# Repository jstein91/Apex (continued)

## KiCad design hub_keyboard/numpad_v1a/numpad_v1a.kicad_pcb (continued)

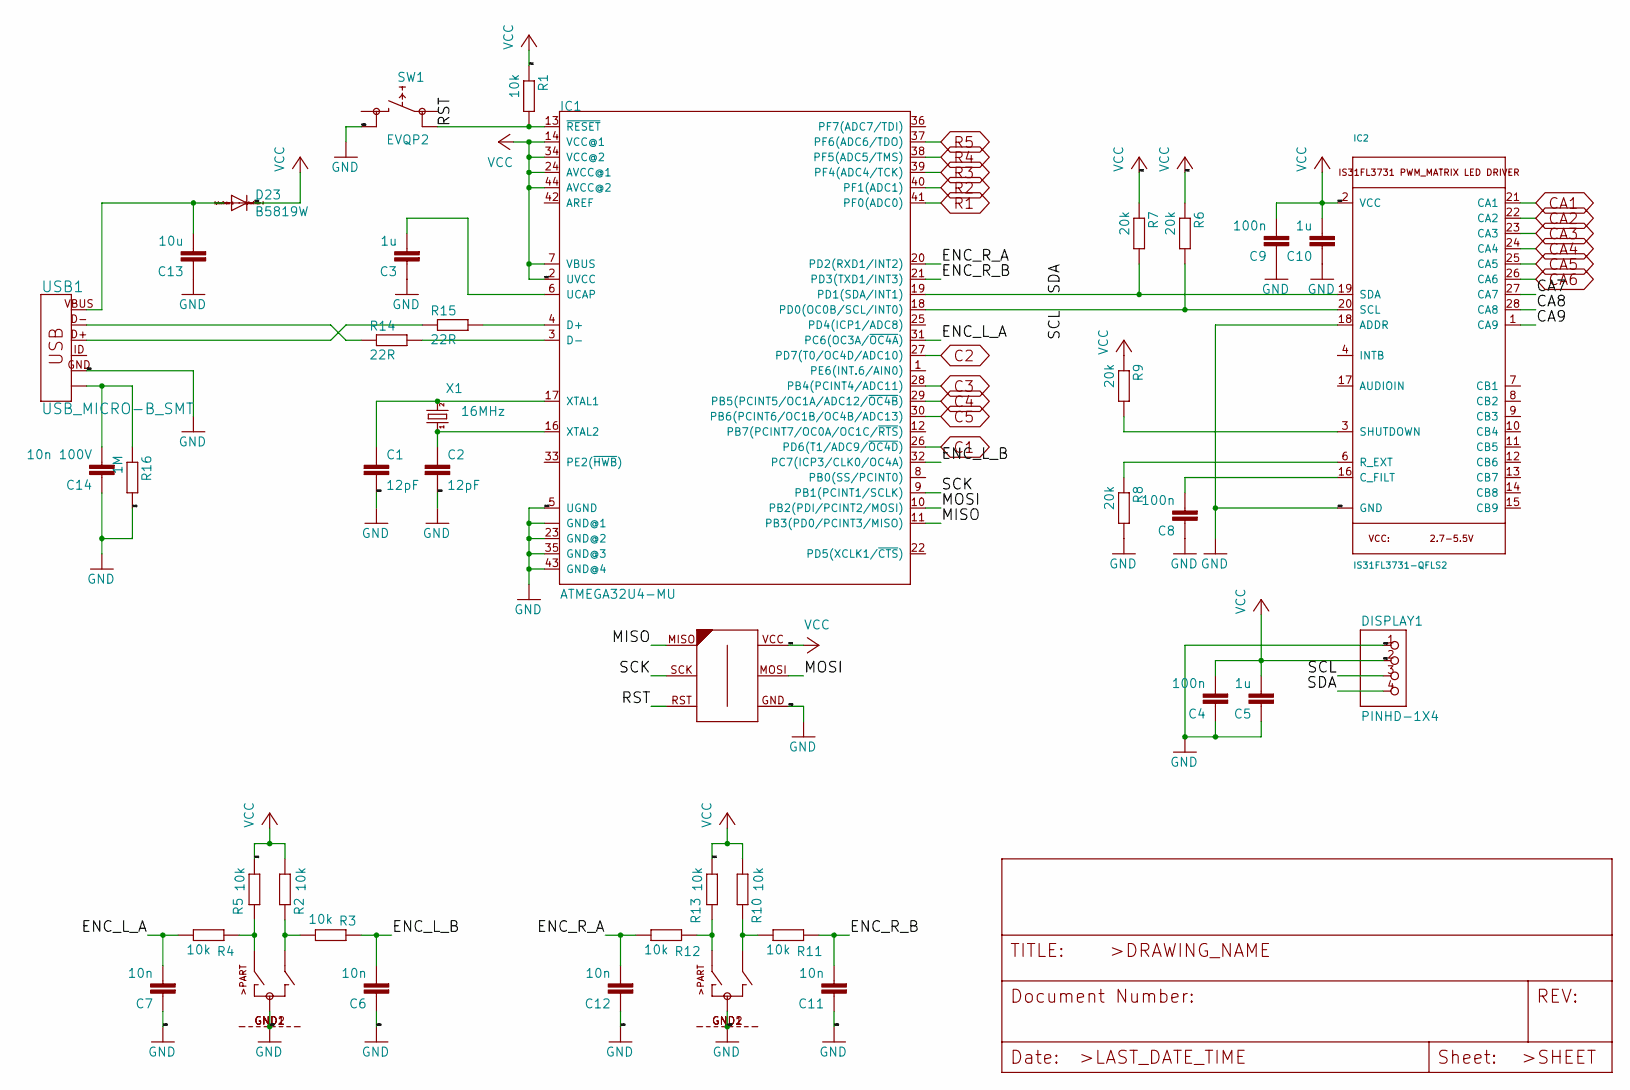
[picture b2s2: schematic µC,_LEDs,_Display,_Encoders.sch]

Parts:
C1, C2: 12pF; C0603; LCSC C38523
C3, C5, C10: 1u; C0603; LCSC C15849
C4, C8, C9: 100n; C0603; LCSC C14663
C6, C7, C11, C12: 10n; C0603; LCSC C57112
C13: 10u; C0603; LCSC C19702
C14: 10n 100V; C0603; LCSC C84709
D23: B5819W; SOD123; LCSC C8598
DISPLAY: PINHD-1X4; 1X04
ENC1, ENC2: EC12E_SW; ALPS_EC12E_SW
IC1: ATMEGA32U4-MU; QFN44G-0.5-7X7MM; LCSC C112161
IC2: IS31FL3731-QFLS2; QFN28_4MM_0.4MM
ISP: AVR-ISP-6-EDGE; 6PAD_ISP
R1, R2, R3, R4, R5, R10, R11, R12, R13: 10k; R0603; LCSC C25804
R6, R7, R8, R9: 20k; R0603; LCSC C4184
R14, R15: 22R; R0603; LCSC C23345
R16: 1M; R0603; LCSC C22935
SW1: EVQP2; FARNELL 2079559
USB: USB_MICRO-B_SMT; USB-MICROB; DIGIKEY 609-4052-1-ND
X1: 16MHz; 3.2X2.5_KX-7; LCSC C13738

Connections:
/µC, LEDs, Display, Encoders/CA7: IC2.27 (CA7)
/µC, LEDs, Display, Encoders/CA8: IC2.28 (CA8)
/µC, LEDs, Display, Encoders/CA9: IC2.1 (CA9)
/µC, LEDs, Display, Encoders/ENC_L_A: C7.2, IC1.31 (PC6(OC3A/~OC4A)), R4.1
/µC, LEDs, Display, Encoders/ENC_L_B: C6.2, IC1.32 (PC7(ICP3/CLK0/OC4A)), R3.2
/µC, LEDs, Display, Encoders/ENC_R_A: C12.2, IC1.20 (PD2(RXD1/INT2)), R12.1
/µC, LEDs, Display, Encoders/ENC_R_B: C11.2, IC1.21 (PD3(TXD1/INT3)), R11.2
/µC, LEDs, Display, Encoders/MISO: IC1.11 (PB3(PD0/PCINT3/MISO)); also elsewhere on the board
/µC, LEDs, Display, Encoders/MOSI: IC1.10 (PB2(PDI/PCINT2/MOSI)); also elsewhere on the board
/µC, LEDs, Display, Encoders/RST: IC1.13 (~RESET), R1.2, SW1.3 (0@B); also elsewhere on the board
/µC, LEDs, Display, Encoders/SCK: IC1.9 (PB1(PCINT1/SCLK)); also elsewhere on the board
/µC, LEDs, Display, Encoders/SCL: IC1.18 (PD0(OC0B/SCL/INT0)), IC2.20 (SCL), R6.2; also elsewhere on the board
/µC, LEDs, Display, Encoders/SDA: IC1.19 (PD1(SDA/INT1)), IC2.19 (SDA), R7.2; also elsewhere on the board
C1: IC1.26 (PD6(T1/ADC9/~OC4D)); also elsewhere on the board
C2: IC1.27 (PD7(T0/OC4D/ADC10)); also elsewhere on the board
C3: IC1.28 (PB4(PCINT4/ADC11)); also elsewhere on the board
C4: IC1.29 (PB5(PCINT5/OC1A/ADC12/~OC4B)); also elsewhere on the board
C5: IC1.30 (PB6(PCINT6/OC1B/OC4B/ADC13)); also elsewhere on the board
CA1: IC2.21 (CA1); also elsewhere on the board
CA2: IC2.22 (CA2); also elsewhere on the board
CA3: IC2.23 (CA3); also elsewhere on the board
CA4: IC2.24 (CA4); also elsewhere on the board
CA5: IC2.25 (CA5); also elsewhere on the board
CA6: IC2.26 (CA6); also elsewhere on the board
GND: C1.2, C2.2, C3.1, C4.1, C5.1, C6.1, C7.1, C8.1, C9.1, C10.1, C11.1, C12.1, C13.1, C14.1, ENC1.C, ENC1.GND1 (G), ENC1.GND2 (G), ENC2.C, ENC2.GND1 (G), ENC2.GND2 (G), IC1.5 (UGND), IC1.15 (GND@1), IC1.23 (GND@2), IC1.35 (GND@3), IC1.43 (GND@4), IC1.TAB (GND@1), IC2.5 (GND), IC2.18 (ADDR), IC2.THERMAL (GND), R8.2, R16.2, SW1.2 (1@B); also elsewhere on the board
unnamed: C1.1, IC1.17 (XTAL1), X1.3 (2)
unnamed: C2.1, IC1.16 (XTAL2), X1.1
unnamed: C3.2, IC1.6 (UCAP)
unnamed: C8.2, IC2.16 (C_FILT)
unnamed 29: C13.2, D23.A; also elsewhere on the board
unnamed 30: C14.2, R16.1; also elsewhere on the board
unnamed: ENC1.A, R12.2, R13.2
unnamed: ENC1.B, R10.2, R11.1
unnamed: ENC2.A, R4.2, R5.2
unnamed: ENC2.B, R2.2, R3.1
unnamed: IC1.3 (D-), R14.2
unnamed: IC1.4 (D+), R15.2
unnamed: IC2.3 (SHUTDOWN), R9.2
unnamed: IC2.6 (R_EXT), R8.1
unnamed 80: R14.1; also elsewhere on the board
unnamed 81: R15.1; also elsewhere on the board
R1: IC1.41 (PF0(ADC0)); also elsewhere on the board
R2: IC1.40 (PF1(ADC1)); also elsewhere on the board
R3: IC1.39 (PF4(ADC4/TCK)); also elsewhere on the board
R4: IC1.38 (PF5(ADC5/TMS)); also elsewhere on the board
R5: IC1.37 (PF6(ADC6/TDO)); also elsewhere on the board
VCC: C4.2, C5.2, C9.2, C10.2, D23.C, IC1.2 (UVCC), IC1.7 (VBUS), IC1.14 (VCC@1), IC1.24 (AVCC@1), IC1.34 (VCC@2), IC1.44 (AVCC@2), IC2.2 (VCC), R1.1, R2.1, R5.1, R6.1, R7.1, R9.1, R10.1, R13.1; also elsewhere on the board

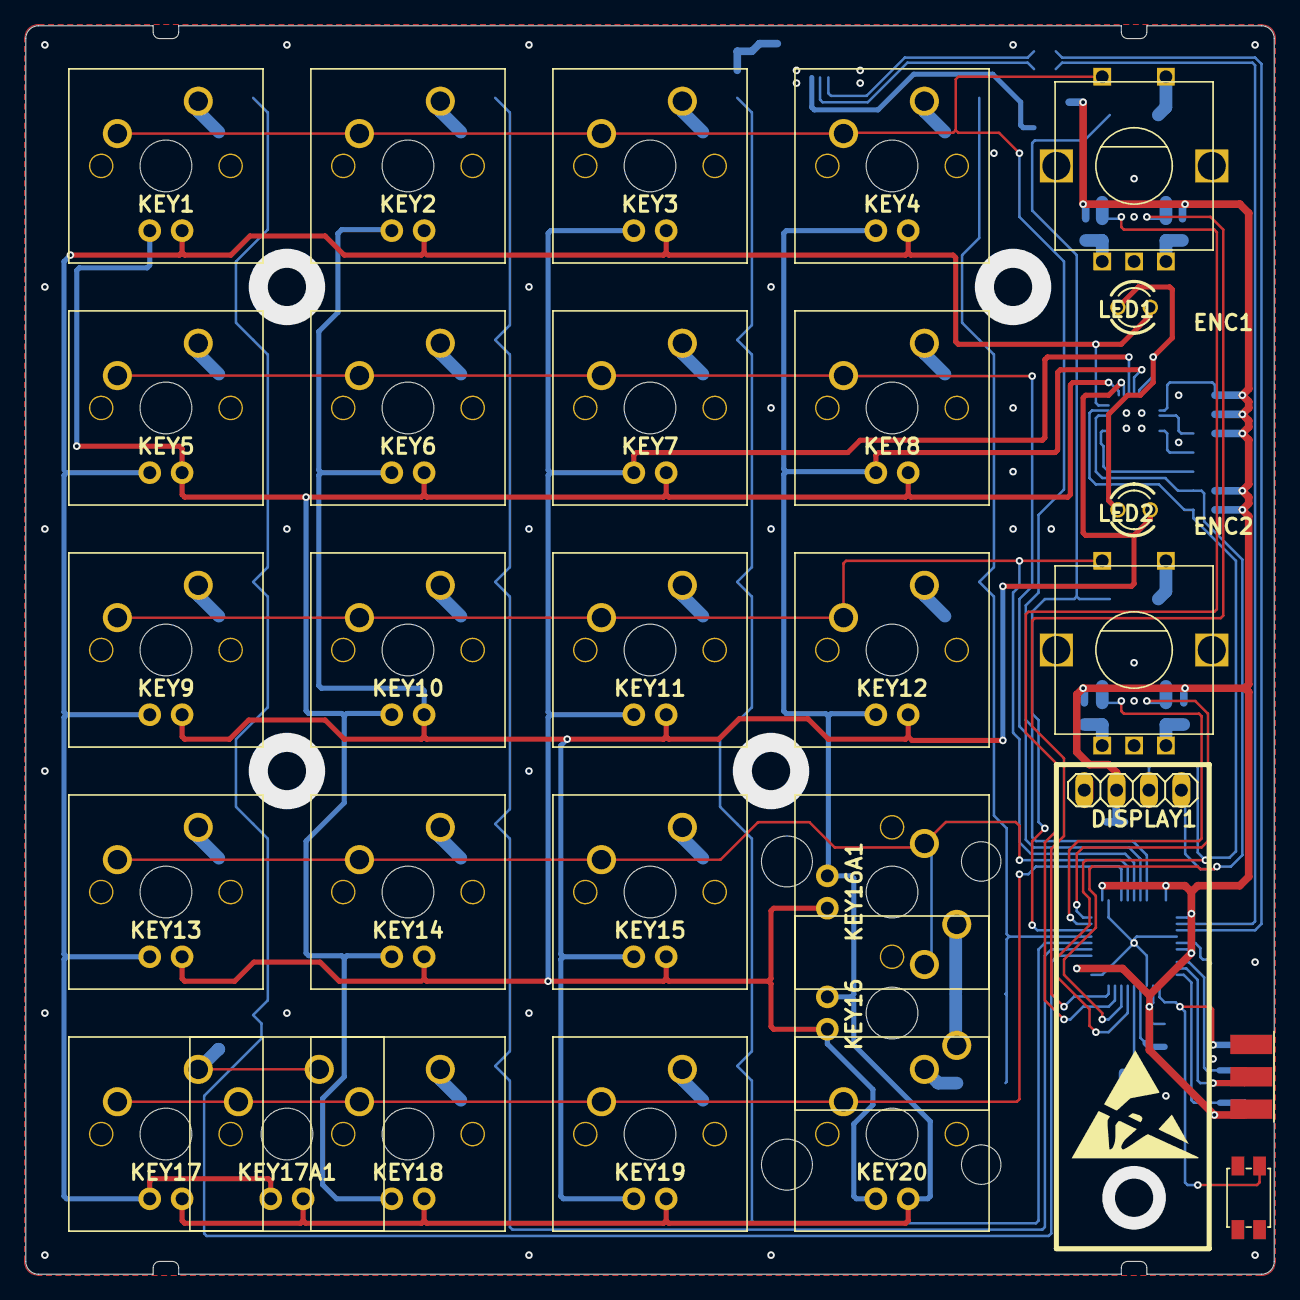
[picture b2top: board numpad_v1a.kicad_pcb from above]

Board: 2 copper layers, 98.0 x 98.0 mm, 91 parts (0 on the bottom side), 66 nets.

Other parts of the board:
@HOLE0, @HOLE1, @HOLE2, @HOLE3: (no value)
DISPLAY1: PINHD-1X4; 1X04
ISP1: AVR-ISP-6-EDGE; 6PAD_ISP
KEY16A1: CHERRY-MX-LED
KEY17A1: CHERRY-MX-LED_NOHOLES
U$1: ESD_10.00
USB1: USB_MICRO-B_SMT; USB-MICROB

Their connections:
/µC, LEDs, Display, Encoders/MISO: ISP1.MISO; also elsewhere on the board
/µC, LEDs, Display, Encoders/MOSI: ISP1.MOSI; also elsewhere on the board
/µC, LEDs, Display, Encoders/RST: ISP1.RST; also elsewhere on the board
/µC, LEDs, Display, Encoders/SCK: ISP1.SCK; also elsewhere on the board
/µC, LEDs, Display, Encoders/SCL: DISPLAY1.3; also elsewhere on the board
/µC, LEDs, Display, Encoders/SDA: DISPLAY1.4; also elsewhere on the board
CA1: KEY17A1.LED+; also elsewhere on the board
CA4: KEY16A1.LED-; also elsewhere on the board
CA5: KEY16A1.LED+, KEY17A1.LED-; also elsewhere on the board
GND: DISPLAY1.1, ISP1.GND, USB1.GND; also elsewhere on the board
unnamed 29: USB1.VBUS; also elsewhere on the board
unnamed 30: USB1.MT1, USB1.MT2, USB1.P$1, USB1.P$2; also elsewhere on the board
unnamed 33: KEY17A1.SW2; also elsewhere on the board
unnamed 34: KEY16A1.SW2; also elsewhere on the board
unnamed 80: USB1.D-; also elsewhere on the board
unnamed 81: USB1.D+; also elsewhere on the board
R4: KEY16A1.SW1; also elsewhere on the board
R5: KEY17A1.SW1; also elsewhere on the board
VCC: DISPLAY1.2, ISP1.VCC; also elsewhere on the board

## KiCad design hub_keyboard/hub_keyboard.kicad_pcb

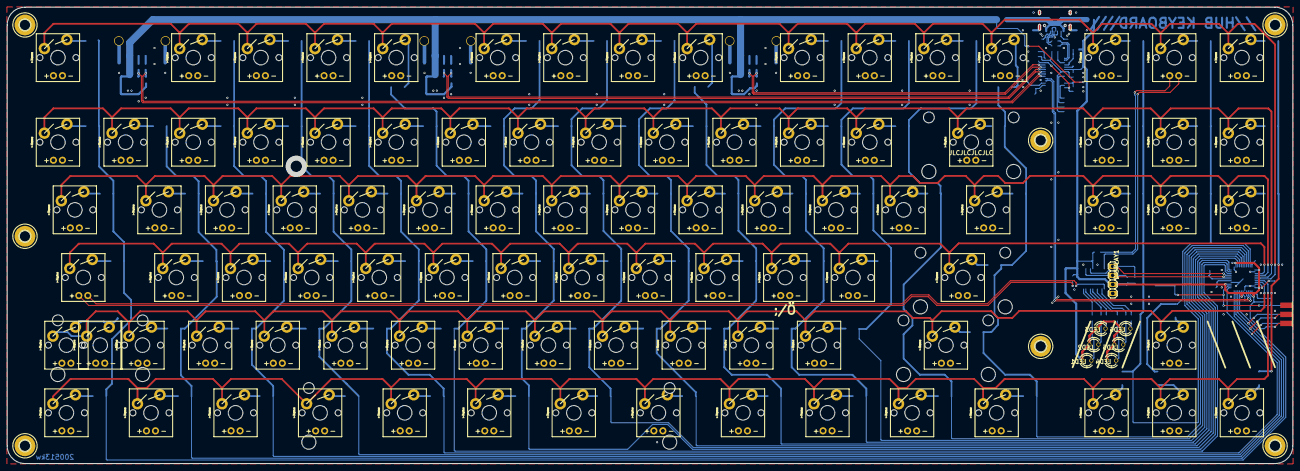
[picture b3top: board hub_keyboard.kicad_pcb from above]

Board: 2 copper layers, 362.0 x 128.5 mm, 280 parts (0 on the bottom side), 178 nets.

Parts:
,/Ä1: MECHANICAL-KEYBOARD1U; CHERRY-MX-LED-1U
-/ß1: MECHANICAL-KEYBOARD1U; CHERRY-MX-LED-1U
.1: MECHANICAL-KEYBOARD1U; CHERRY-MX-LED-1U
//-1: MECHANICAL-KEYBOARD1U; CHERRY-MX-LED-1U
</,1: MECHANICAL-KEYBOARD1U; CHERRY-MX-LED-1U
<>1: MECHANICAL-KEYBOARD1U; CHERRY-MX-LED-1U
=/´1: MECHANICAL-KEYBOARD1U; CHERRY-MX-LED-1U
>/.1: MECHANICAL-KEYBOARD1U; CHERRY-MX-LED-1U
@HOLE0, @HOLE1, @HOLE2, @HOLE3, @HOLE4, @HOLE5, @HOLE6: (no value)
A1: MECHANICAL-KEYBOARD1U; CHERRY-MX-LED-1U
B1: MECHANICAL-KEYBOARD1U; CHERRY-MX-LED-1U
BACKSPACE1: MECHANICAL-KEYBOARD2U; CHERRY-MX-LED-1X2U
C1, C4, C6, C8: 10n 100V; C0603
C2, C10, C15, C19: 100nF; C0603
C3, C5, C7: 100uF; CT3528
C9, C16, C17, C18: 12pF; C0603
C11, C12, C13: 10u; C0603
C14: 10n; C0603
C20: 1u; C0603
C21: MECHANICAL-KEYBOARD1U; CHERRY-MX-LED-1U
CAPSLOCK1: MECHANICAL-KEYBOARD1.75U; CHERRY-MX-LED-1.75U
D1, D2, D3, D4, D5, D6, D7, D8, D9, D10, D11, D12, D13, D15, D17, D19, D20, D21, D22, D23, D24, D25, D26, D27, D28, D29, D30, D31, D32, D33, D34, D35, D36, D37, D38, D39, D40, D41, D42, D43, D44, D45, D46, D47, D48, D49, D50, D51, D52, D53, D54, D55, D56, D57, D58, D59, D60, D61, D62, D63, D64, D65, D66, D67, D68, D69, D70, D71, D72, D73, D74, D75, D76, D77, D78, D79, D80, D81, D82, D83, D84, D85, D86, D87, D88, D89, D90, D91, D92, D93, D94, D95: 1N4148; SOD123
D14, D16, D18: PRTR5V0U2X; SOT143
D96: MECHANICAL-KEYBOARD1U; CHERRY-MX-LED-1U
D-ARR1: MECHANICAL-KEYBOARD1U; CHERRY-MX-LED-1U
DELETE1: MECHANICAL-KEYBOARD1U; CHERRY-MX-LED-1U
DISPLAY1: I2C_OLED_128X32; 128X32_I2C_OLED
DOWN1: MECHANICAL-KEYBOARD1U; CHERRY-MX-LED-1U
E1: MECHANICAL-KEYBOARD1U; CHERRY-MX-LED-1U
END1: MECHANICAL-KEYBOARD1U; CHERRY-MX-LED-1U
ESC1: MECHANICAL-KEYBOARD1U; CHERRY-MX-LED-1U
F1: 1.1A Hold; R1210
F2: MECHANICAL-KEYBOARD1U; CHERRY-MX-LED-1U
F_1, F_2, F_3, F_4, F_5, F_6, F_7, F_8, F_9, F_10, F_11, F_12: MECHANICAL-KEYBOARD1U; CHERRY-MX-LED-1U
G1: MECHANICAL-KEYBOARD1U; CHERRY-MX-LED-1U
H1, H2, H3, H4, H5, H6, H7: MOUNT-PAD-ROUND3.2; 3,2-PAD
H8: MECHANICAL-KEYBOARD1U; CHERRY-MX-LED-1U
HOME1: MECHANICAL-KEYBOARD1U; CHERRY-MX-LED-1U
I1: MECHANICAL-KEYBOARD1U; CHERRY-MX-LED-1U
IC1: FE1.1S; SSOP28
IC2: 24SN; SO-08
IC3: PCF8574APWR; SSOP20
IC4: ATMEGA32U4-MU; QFN44G-0.5-7X7MM
INSERT1: MECHANICAL-KEYBOARD1U; CHERRY-MX-LED-1U
ISP1: AVR-ISP-6-EDGE; 6PAD_ISP
J1, J2, J3: USB_A_SMT_FEMALE; USB-A-S-SILK-FEMALE
J4: USB_C2-LAYER; USB-C-16P
J5: MECHANICAL-KEYBOARD1U; CHERRY-MX-LED-1U
K1: MECHANICAL-KEYBOARD1U; CHERRY-MX-LED-1U
L1: MECHANICAL-KEYBOARD1U; CHERRY-MX-LED-1U
L-ALT1: MECHANICAL-KEYBOARD1.25U; CHERRY-MX-LED-1.25U
L-CTRL1: MECHANICAL-KEYBOARD1.25U; CHERRY-MX-LED-1.25U
L-OS1: MECHANICAL-KEYBOARD1.25U; CHERRY-MX-LED-1.25U
L-SHIFT1: MECHANICAL-KEYBOARD1.25U; CHERRY-MX-LED-1.25U
L-SHIFT2: MECHANICAL-KEYBOARD2.25U; CHERRY-MX-LED-1X2.25
LED1, LED2, LED3, LED4, LED5, LED6: LED3MM
LS1, LS2: MECHANICAL-KEYBOARD1.25U; CHERRY-MX-LED-1.25U
L_ARR1: MECHANICAL-KEYBOARD1U; CHERRY-MX-LED-1U
M1: MECHANICAL-KEYBOARD1U; CHERRY-MX-LED-1U
MENU1: MECHANICAL-KEYBOARD1.25U; CHERRY-MX-LED-1.25U
N1: MECHANICAL-KEYBOARD1U; CHERRY-MX-LED-1U
O1: MECHANICAL-KEYBOARD1U; CHERRY-MX-LED-1U
P1: MECHANICAL-KEYBOARD1U; CHERRY-MX-LED-1U
PAUSE1: MECHANICAL-KEYBOARD1U; CHERRY-MX-LED-1U
PRINT1: MECHANICAL-KEYBOARD1U; CHERRY-MX-LED-1U
Q1: MECHANICAL-KEYBOARD1U; CHERRY-MX-LED-1U
R1: 2k7; R0603
R2, R6: 5k1; R0603
R3, R4, R11, R12, R14, R15, R17, R18: 22R; R0603
R5, R24, R25: 20k; R0603
R7, R20, R21, R33: 10k; R0603
R8, R10, R13, R16: 1M; R0603
R9: Ferrite 2A; R0805
R19: 100k; R0603
R22, R23, R26, R27, R28, R29, R30, R31, R32: 1k; R0603
R34: MECHANICAL-KEYBOARD1U; CHERRY-MX-LED-1U
R-ALT1: MECHANICAL-KEYBOARD1.25U; CHERRY-MX-LED-1.25U
R-CTRL1: MECHANICAL-KEYBOARD1.25U; CHERRY-MX-LED-1.25U
R-OS1: MECHANICAL-KEYBOARD1.25U; CHERRY-MX-LED-1.25U
R-SHIFT1: MECHANICAL-KEYBOARD2.75U; CHERRY-MX-LED-1X2.75
RESET1: MOMENTARY-SWITCH-SPST-SMD-5.2-REDUNDANT; TACTILE_SWITCH_SMD_5.2MM
RETURN1: MECHANICAL-KEYBOARD2.25U; CHERRY-MX-LED-1X2.25
RS1, RS2: MECHANICAL-KEYBOARD1.25U; CHERRY-MX-LED-1.25U
R_ARR1: MECHANICAL-KEYBOARD1U; CHERRY-MX-LED-1U
S1: STABILIZER-1X2U; STABILIZER_1X2U
S2, S3: STABILIZER-1X2.25U; STABILIZER_1X2.25U
S4: STABILIZER-1X2.75U; STABILIZER_1X2.75U
S5: STABILIZER-1X6.25U; STABILIZER_1X6.25U
S6: MECHANICAL-KEYBOARD1U; CHERRY-MX-LED-1U
SCROLL1: MECHANICAL-KEYBOARD1U; CHERRY-MX-LED-1U
SPACE1: MECHANICAL-KEYBOARD6.25U; CHERRY-MX-LED-1X6.25
T1: MECHANICAL-KEYBOARD1U; CHERRY-MX-LED-1U
TAB1: MECHANICAL-KEYBOARD1.5U; CHERRY-MX-LED-1.5U
U1: MECHANICAL-KEYBOARD1U; CHERRY-MX-LED-1U
UNK0, UNK1, UNK2, UNK3, UNK4, UNK5, UNK6, UNK7, UNK8, UNK9: MECHANICAL-KEYBOARD1U; CHERRY-MX-LED-1U
UP1: MECHANICAL-KEYBOARD1U; CHERRY-MX-LED-1U
U_ARR1: MECHANICAL-KEYBOARD1U; CHERRY-MX-LED-1U
V1: MECHANICAL-KEYBOARD1U; CHERRY-MX-LED-1U
W1: MECHANICAL-KEYBOARD1U; CHERRY-MX-LED-1U
X1: 12MHz; 3.2X2.5_KX-7
X2: 16MHz; 3.2X2.5_KX-7
X3: MECHANICAL-KEYBOARD1U; CHERRY-MX-LED-1U
Y/Z1: MECHANICAL-KEYBOARD1U; CHERRY-MX-LED-1U
Z/Y1: MECHANICAL-KEYBOARD1U; CHERRY-MX-LED-1U
[/Ü1: MECHANICAL-KEYBOARD1U; CHERRY-MX-LED-1U
\\/#1: MECHANICAL-KEYBOARD1.5U; CHERRY-MX-LED-1.5U
]/+1: MECHANICAL-KEYBOARD1U; CHERRY-MX-LED-1U
`/^1: MECHANICAL-KEYBOARD1U; CHERRY-MX-LED-1U

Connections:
/hub_keyboard_2/1V8_HUB: C11.2, C15.2, IC1.12, IC1.28
/hub_keyboard_2/3V3_HUB: C10.2, C13.2, IC1.13, IC1.21, IC2.7, IC2.8, R5.1
/hub_keyboard_2/RST: IC4.13, ISP1.RST, R33.2, RESET1.1, RESET1.2
/hub_keyboard_2/SCL: DISPLAY1.3, IC3.2, IC4.18, R24.2
/hub_keyboard_2/SCL_HUB: IC1.23, IC2.6
/hub_keyboard_2/SDA: DISPLAY1.4, IC3.4, IC4.19, R25.2
/hub_keyboard_2/SDA_HUB: IC1.27, IC2.5
C1: D1.C, D20.C, D37.C, D54.C, D67.C, D81.C, IC4.8
C2/SCK: D21.C, D38.C, D55.C, D68.C, D82.C, IC4.9, ISP1.SCK
C3/MOSI: D2.C, D22.C, D39.C, D56.C, D69.C, D83.C, IC4.10, ISP1.MOSI
C4/MISO: D3.C, D23.C, D40.C, D57.C, D70.C, D84.C, IC4.11, ISP1.MISO
C5: D4.C, D24.C, D41.C, D58.C, D71.C, D85.C, IC4.12
C6: D15.C, D25.C, D42.C, D59.C, D72.C, IC4.20
C7: D5.C, D26.C, D43.C, D60.C, D73.C, D86.C, IC4.21
C8: D6.C, D27.C, D44.C, D61.C, D74.C, D87.C, IC4.22
C9: D7.C, D28.C, D45.C, D62.C, D75.C, D88.C, IC4.25
C10: D17.C, D29.C, D46.C, D63.C, D76.C, D89.C, IC4.26
C11: D8.C, D30.C, D47.C, D64.C, D77.C, D90.C, IC4.27
C12: D9.C, D31.C, D48.C, D65.C, D78.C, IC4.28
C13: D10.C, D32.C, D49.C, D91.C, IC4.29
C14: D19.C, D33.C, D50.C, D66.C, D79.C, D92.C, IC4.30
C15: D11.C, D34.C, D51.C, D93.C, IC4.31
C16: D12.C, D35.C, D52.C, D80.C, D94.C, IC4.32
C17: D13.C, D36.C, D53.C, D95.C, IC4.1
CL_LED_A: CAPSLOCK1.A, R22.1
CL_LED_C: CAPSLOCK1.K, IC3.11
GND: C1.1, C2.1, C3.-, C4.1, C5.-, C6.1, C7.-, C8.1, C9.2, C10.1, C11.1, C12.1, C13.1, C14.1, C15.1, C16.2, C17.2, C18.2, C19.1, C20.1, D14.1, D16.1, D18.1, DISPLAY1.1, IC1.1, IC2.1, IC2.2, IC2.3, IC2.4, IC3.6, IC3.7, IC3.9, IC3.15, IC4.5, IC4.15, IC4.23, IC4.35, IC4.43, IC4.TAB, ISP1.GND, J1.GND, J2.GND, J3.GND, J4.GND, J4.GND2, R1.1, R2.1, R6.1, R8.2, R10.2, R13.2, R16.2, R19.1, R20.2, R26.1, RESET1.3, RESET1.4
unnamed: ,/Ä1.S2, D65.A
unnamed: -/ß1.S2, D31.A
unnamed: .1.S2, D64.A
unnamed: //-1.S2, D78.A
unnamed: </,1.S2, D76.A
unnamed: <>1.S2, D68.A
unnamed: =/´1.S2, D32.A
unnamed: >/.1.S2, D77.A
unnamed: A1.S2, D55.A
unnamed: B1.S2, D73.A
unnamed: BACKSPACE1.S2, D33.A
unnamed: C1.2, J4.SHLD1, J4.SHLD2, J4.SHLD3, J4.SHLD4, J4.SHLD5, J4.SHLD6, J4.SHLD7, J4.SHLD8, R8.1
unnamed: C2.2, IC1.18, R7.1, R19.2
unnamed: C3.+, C5.+, C7.+, D14.4, D16.4, D18.4, F1.1, J1.VBUS, J2.VBUS, J3.VBUS, R21.2
unnamed: C4.2, J1.SHLD1, J1.SHLD2, R10.1
unnamed: C6.2, J2.SHLD1, J2.SHLD2, R13.1
unnamed: C8.2, J3.SHLD1, J3.SHLD2, R16.1
unnamed: C9.1, IC1.3, X1.3
unnamed: C14.2, IC1.26, R21.1
unnamed: C16.1, IC1.2, X1.1
unnamed: C17.1, IC4.17, X2.3
unnamed: C18.1, IC4.16, X2.1
unnamed: C19.2, IC4.42
unnamed: C20.2, IC4.6
unnamed: C21.S2, D71.A
unnamed: CAPSLOCK1.S2, D54.A
unnamed: D1.A, ESC1.S2
unnamed: D2.A, F_1.S2
unnamed: D3.A, F_2.S2
unnamed: D4.A, F_3.S2
unnamed: D5.A, F_5.S2
unnamed: D6.A, F_6.S2
unnamed: D7.A, F_7.S2
unnamed: D8.A, F_9.S2
unnamed: D9.A, F_10.S2
unnamed: D10.A, F_11.S2
unnamed: D11.A, PRINT1.S2
unnamed: D12.A, SCROLL1.S2
unnamed: D13.A, PAUSE1.S2
unnamed: D14.2, IC1.6, R11.1
unnamed: D14.3, IC1.7, R12.1
unnamed: D15.A, F_4.S2
unnamed: D16.2, IC1.8, R14.1
unnamed: D16.3, IC1.9, R15.1
unnamed: D17.A, F_8.S2
unnamed: D18.2, IC1.10, R17.1
unnamed: D18.3, IC1.11, R18.1
unnamed: D19.A, F_12.S2
unnamed: D20.A, `/^1.S2
unnamed: D21.A, UNK1.S2
unnamed: D22.A, UNK2.S2
unnamed: D23.A, UNK3.S2
unnamed: D24.A, UNK4.S2
unnamed: D25.A, UNK5.S2
unnamed: D26.A, UNK6.S2
unnamed: D27.A, UNK7.S2
unnamed: D28.A, UNK8.S2
unnamed: D29.A, UNK9.S2
unnamed: D30.A, UNK0.S2
unnamed: D34.A, INSERT1.S2
unnamed: D35.A, HOME1.S2
unnamed: D36.A, UP1.S2
unnamed: D37.A, TAB1.S2
unnamed: D38.A, Q1.S2
unnamed: D39.A, W1.S2
unnamed: D40.A, E1.S2
unnamed: D41.A, R34.S2
unnamed: D42.A, T1.S2
unnamed: D43.A, Z/Y1.S2
unnamed: D44.A, U1.S2
unnamed: D45.A, I1.S2
unnamed: D46.A, O1.S2
unnamed: D47.A, P1.S2
unnamed: D48.A, [/Ü1.S2
unnamed: D49.A, ]/+1.S2
unnamed: D50.A, \\/#1.S2
unnamed: D51.A, DELETE1.S2
unnamed: D52.A, END1.S2
unnamed: D53.A, DOWN1.S2
unnamed: D56.A, S6.S2
unnamed: D57.A, D96.S2
unnamed: D58.A, F2.S2
unnamed: D59.A, G1.S2
unnamed: D60.A, H8.S2
unnamed: D61.A, J5.S2
unnamed: D62.A, K1.S2
unnamed: D63.A, L1.S2
unnamed: D66.A, RETURN1.S2
unnamed: D67.A, L-SHIFT1.S2, L-SHIFT2.S2
unnamed: D69.A, Y/Z1.S2
unnamed: D70.A, X3.S2
unnamed: D72.A, V1.S2
unnamed: D74.A, N1.S2
unnamed: D75.A, M1.S2
unnamed: D79.A, R-SHIFT1.S2
unnamed: D80.A, U_ARR1.S2
unnamed: D81.A, L-CTRL1.S2
unnamed: D82.A, L-OS1.S2
unnamed: D83.A, L-ALT1.S2
unnamed: D84.A, LS1.S2
unnamed: D85.A, LS2.S2
unnamed: D86.A, SPACE1.S2
unnamed: D87.A, RS1.S2
unnamed: D88.A, RS2.S2
unnamed: D89.A, R-ALT1.S2
unnamed: D90.A, R-OS1.S2
unnamed: D91.A, MENU1.S2
unnamed: D92.A, R-CTRL1.S2
unnamed: D93.A, L_ARR1.S2
unnamed: D95.A, R_ARR1.S2
unnamed: D94.A, D-ARR1.S2
unnamed: F1.2, J4.VBUS1, J4.VBUS2, R9.2
unnamed: IC1.4, IC4.3
unnamed: IC1.5, IC4.4
unnamed: IC1.14, R1.2
unnamed: IC1.15, R4.1
unnamed: IC1.16, R3.1
unnamed: IC1.17, R5.2
unnamed: IC1.19, R20.1
unnamed: IC3.12, R32.1
unnamed: IC3.14, R31.1
unnamed: IC3.16, R30.1
unnamed: IC3.17, R29.1
unnamed: IC3.19, R28.1
unnamed: IC3.20, R27.1
unnamed: IC4.33, R26.2
unnamed: J1.D+, R12.2
unnamed: J1.D-, R11.2
unnamed: J2.D+, R15.2
unnamed: J2.D-, R14.2
unnamed: J3.D+, R18.2
unnamed: J3.D-, R17.2
unnamed: J4.A5, R2.2
unnamed: J4.A6, J4.B6, R3.2
unnamed: J4.A7, J4.B7, R4.2
unnamed: J4.B5, R6.2
unnamed: LED1.K, R27.2
unnamed: LED2.K, R28.2
unnamed: LED3.K, R29.2
unnamed: LED4.K, R30.2
unnamed: LED5.K, R31.2
unnamed: LED6.K, R32.2
R1: ESC1.S1, F_1.S1, F_2.S1, F_3.S1, F_4.S1, F_5.S1, F_6.S1, F_7.S1, F_8.S1, F_9.S1, F_10.S1, F_11.S1, F_12.S1, IC4.39, PAUSE1.S1, PRINT1.S1, SCROLL1.S1
R2: -/ß1.S1, =/´1.S1, BACKSPACE1.S1, HOME1.S1, IC4.38, INSERT1.S1, UNK0.S1, UNK1.S1, UNK2.S1, UNK3.S1, UNK4.S1, UNK5.S1, UNK6.S1, UNK7.S1, UNK8.S1, UNK9.S1, UP1.S1, `/^1.S1
R3: DELETE1.S1, DOWN1.S1, E1.S1, END1.S1, I1.S1, IC4.37, O1.S1, P1.S1, Q1.S1, R34.S1, T1.S1, TAB1.S1, U1.S1, W1.S1, Z/Y1.S1, [/Ü1.S1, \\/#1.S1, ]/+1.S1
R4: ,/Ä1.S1, .1.S1, A1.S1, CAPSLOCK1.S1, D96.S1, F2.S1, G1.S1, H8.S1, IC4.36, J5.S1, K1.S1, L1.S1, RETURN1.S1, S6.S1
R5: //-1.S1, </,1.S1, <>1.S1, >/.1.S1, B1.S1, C21.S1, IC4.41, L-SHIFT1.S1, L-SHIFT2.S1, M1.S1, N1.S1, R-SHIFT1.S1, U_ARR1.S1, V1.S1, X3.S1, Y/Z1.S1
R6: D-ARR1.S1, IC4.40, L-ALT1.S1, L-CTRL1.S1, L-OS1.S1, LS1.S1, LS2.S1, L_ARR1.S1, MENU1.S1, R-ALT1.S1, R-CTRL1.S1, R-OS1.S1, RS1.S1, RS2.S1, R_ARR1.S1, SPACE1.S1
SL_LED_A: R23.1, SCROLL1.A
SL_LED_C: IC3.10, SCROLL1.K
VCC: C12.2, DISPLAY1.2, IC1.20, IC3.5, IC4.2, IC4.7, IC4.14, IC4.24, IC4.34, IC4.44, ISP1.VCC, LED1.A, LED2.A, LED3.A, LED4.A, LED5.A, LED6.A, R7.2, R9.1, R22.2, R23.2, R24.1, R25.1, R33.1

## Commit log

2020-07-06 Updated matrix and ground
    Updated key matrix(WIP). Replaced GND on USB hub sch with correct GND symbol.
2020-07-06 Update matrix and MCU
    Updated matrix. Added decoupling capacitors. Added Encoder.
2020-07-06 Begin annotation
    Annotated schematic and began associating symbols with footprints.
2020-07-06 Assign Footprints
    Continued assigning footprints
2020-07-07 Associate FP
    added debounce to encoder. finalized footrpint association.
2020-07-07 created datasheet folder
2020-07-07 Upload datasheets
    Uploaded datasheets for the MCU and the USB hub controller
2020-07-07 No connects and footprints
    Added no connects and associated all footprints.
2020-07-07 Fixed symbols
    Re-wired MCU XTAL and corrected footprints
2020-07-08 switch layout
    layed out switches only
2020-07-08 usb layout
2020-07-08 Plane add
    added ground plane and edge cuts. refined USB placement.
2020-07-08 Placed Caps
    Arranged decoupling capacitors around MCU and for encoder and OLED
2020-07-08 refined diode placement
2020-07-08 Changed from hotswap to normal switch
2020-07-08 finished switch diode placement
2020-07-09 Update sym-lib-table
    Added acheron symbols to project library
2020-07-09 add daughter board
    Updated schematic and pcb to remove onboard usb c nd replace with connector to use unified C board
2020-07-10 removed 1 usb
    Removed 1 USB from hub and made rotary bump less pronounced
2020-07-10 Rotated switchs to south facing
2020-07-10 reworked crystal
2020-07-10 routed crystal area and decoupling caps
2020-07-11 route hub
    routed usb hub
2020-07-11 add ground plane
2020-07-11 hub controller placement
2020-07-11 refine sub hub
2020-07-13 route keys
2020-07-13 routed keys
2020-07-14 assigned some pins
2020-07-14 completed routing matrix
2020-07-14 Add ISP header
2020-07-14 Update fp-info-cache
2020-07-15 silkscreen
2020-07-20 refined silkscreens
2020-07-23 Fill zones
    Removed large fill zone and created one small one for XTAL area and larger one for whole board
